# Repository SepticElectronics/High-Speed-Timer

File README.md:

# High Speed Precision Timer SEHSPT554

A simple digital timer based on the TDC7200 for high-precision, short burst time measurement with a resolution of up to 55 ps. 
Long interval, low precision time measurement is done using a 125 MHz oscillator and a DDR-type clocked synchronous counter, implemented in a MachXO2 FPGA with a theoretical resolution of 4 ns.
The data collection and interfacing is handled by an ATSAM4S Microcontroller.
Two USB 2.0 and a MicroSD Interface are available for data collection.

If connected to a PC via USB-B the device is fully USB-Bus-powered.
In the case of only using a microSD-Card or a USB thumb drive, the device must be powered from a 6-24 V Barrel Connector (5.5 x 2.1 mm or 5.5 x 2.5 mm, Center Positive).

A MIPI10 JTAG programming header is available and can be used for reprogramming the FPGA or for a boundary scan of both the FPGA and the MCU. 
A 4-Pin (2.54 mm) UART connector is provided for reprogramming the MCU.
Three SMA connectors are used with 3.3 V LVCMOS signal-level for triggering and resetting the measurements.

The PCB is designed to fit inside the Thorlabs EEB3311 housing.

*This project started out as a Product Design / Layout challenge for myself and is still in a very early WIP-stage. Any (constructive) input is very much appreciated.*
**Please note that all of the mentioned features are purely implemented on a PCB / Schematic level. No software, except for the FPGA configuration, has been written yet.**

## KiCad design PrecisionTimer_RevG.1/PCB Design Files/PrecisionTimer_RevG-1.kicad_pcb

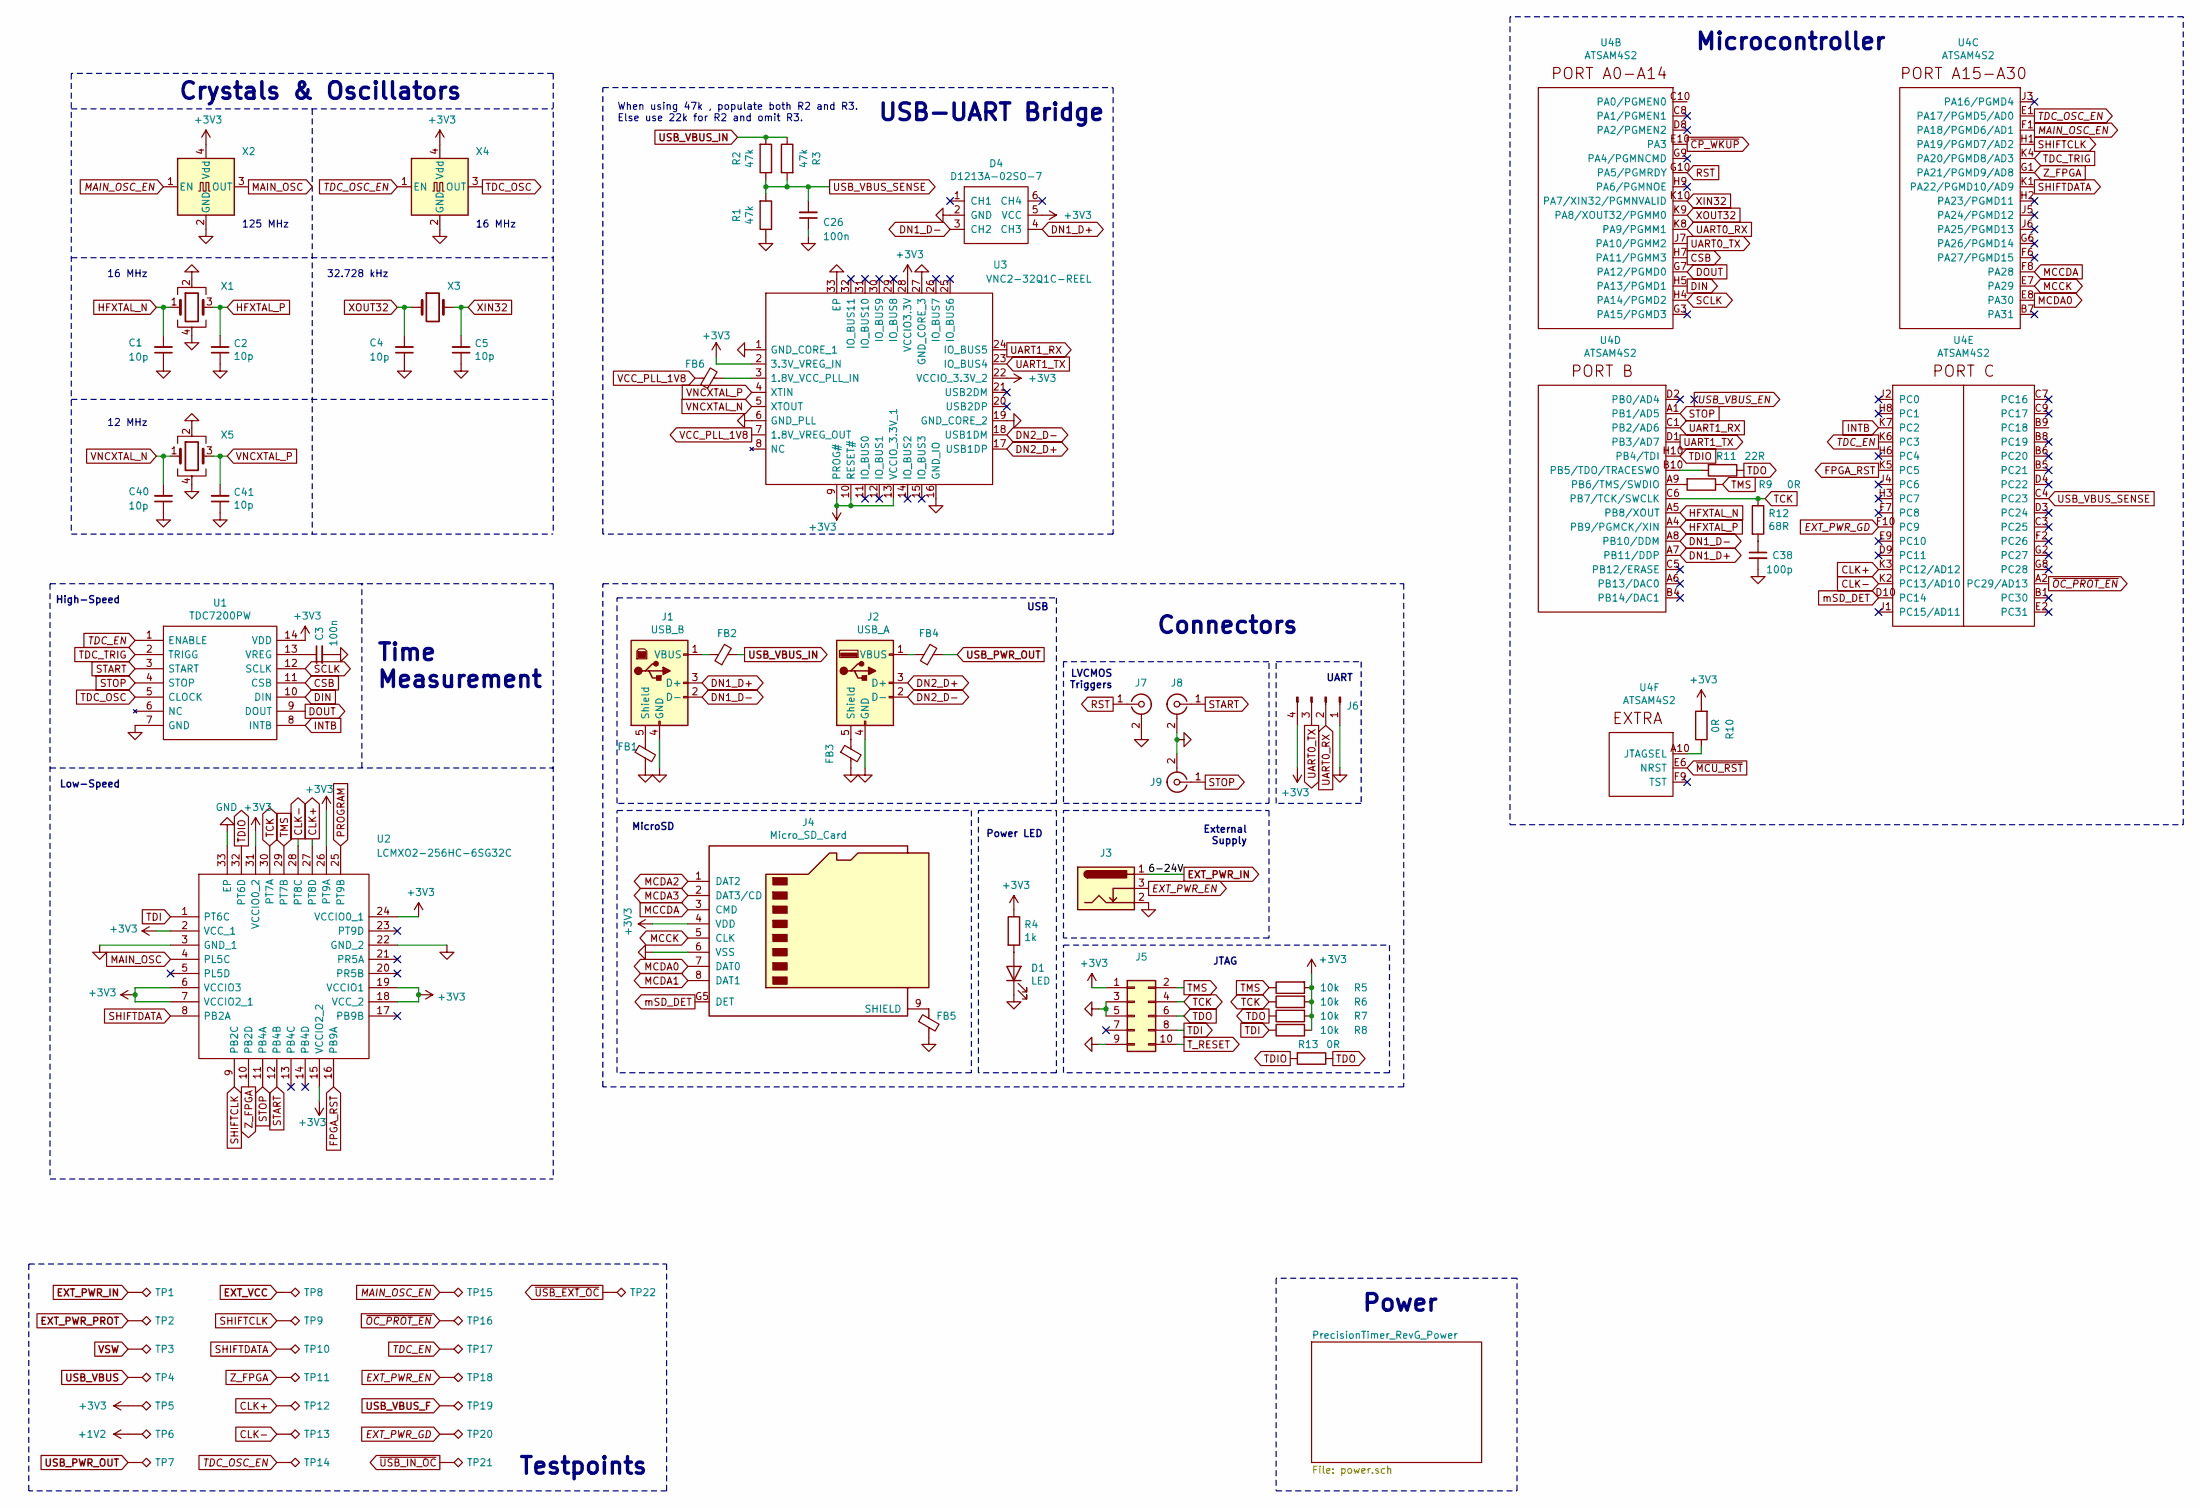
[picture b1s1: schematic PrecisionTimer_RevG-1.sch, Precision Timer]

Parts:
C1, C2, C4, C5, C40, C41: 10p; C_0402_1005Metric
C3, C26: 100n; C_0603_1608Metric
C38: 100p; C_0603_1608Metric
D1: LED; LED_D3.0mm
D4: D1213A-02SO-7; SOT-26
FB1, FB2, FB3, FB4, FB5, FB6: Ferrite 2A 330R; L_0603_1608Metric
J1: USB_B; KUSBEXSMTBS1NBTR
J2: USB_A; USB_A_Molex_67643_Horizontal
J3: Barrel_Jack_Switch; BarrelJack_Wuerth_6941xx301002
J4: Micro_SD_Card; 475710001
J5: Conn_02x05_Odd_Even; PinHeader_2x05_P1.27mm_Vertical_SMD
J6: Conn_01x04_Male; PinHeader_1x04_P2.54mm_Vertical_SMD_Pin1Left
J7, J8, J9: Conn_Coaxial; SMA_Molex_73251-2200_Horizontal
R1, R2, R3: 47k; R_0402_1005Metric
R4: 1k; R_0603_1608Metric
R5, R6, R7, R8: 10k; R_0603_1608Metric
R9, R10, R13: 0R; R_0603_1608Metric
R11: 22R; R_0603_1608Metric
R12: 68R; R_0603_1608Metric
TP1, TP3, TP5, TP6, TP12, TP13, TP14, TP15, TP21, TP22: TestPoint_Alt; TestPoint_Pad_D0.7mm
TP2, TP4, TP7, TP8, TP9, TP10, TP11, TP16, TP17, TP18, TP19, TP20: TestPoint_Alt; TestPoint_Pad_D1.0mm
U1: TDC7200PW; SOP65P640X120-14N; Manufacturer_Part_Number TDC7200PW
U2: LCMXO2-256HC-6SG32C; QFN50P500X500X60-33N; Manufacturer_Part_Number LCMXO2-256HC-4SG32I
U3: VNC2-32Q1C-REEL; QFN65P700X700X90-33N-D; Manufacturer_Part_Number VNC2-32Q1C-REEL; Mouser Part Number 895-VNC2-32Q1C-REEL
U4: ATSAM4S2; TFBGA-100_9.0x9.0mm_Layout10x10_P0.8mm
X1, X5: ECS-160-8-36B-CKY-TR; Crystal_SMD_2520-4Pin_2.5x2.0mm
X2: DSC1001DI2-125.0000; Oscillator_SMD_SeikoEpson_SG210-4Pin_2.5x2.0mm
X3: FC-135 32.7680KA-AG0; Crystal_SMD_3215-2Pin_3.2x1.5mm
X4: ECS-3225S33-160-FN-TR; Oscillator_SMD_EuroQuartz_XO32-4Pin_3.2x2.5mm

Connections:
+1V2: TP6.1; also elsewhere on the board
+3V3: D4.5 (VCC), J4.4 (VDD), J5.1, J6.4, R4.1, R5.2, R6.2, R7.2, R8.2, R10.2, TP5.1, U1.14 (VDD), U2.2 (VCC_1), U2.6 (VCCIO3), U2.7 (VCCIO2_1), U2.15 (VCCIO2_2), U2.18 (VCC_2), U2.19 (VCCIO1), U2.24 (VCCIO0_1), U2.26 (PT9A), U2.31 (VCCIO0_2), U3.2 (3.3V_VREG_IN), U3.9 (PROG#), U3.10 (RESET#), U3.13 (VCCIO_3.3V_1), U3.22 (VCCIO_3.3V_2), U3.28 (VCCIO3.3V), X2.4 (Vdd), X4.4 (Vdd); also elsewhere on the board
CLK+: TP12.1, U2.27 (PT8D), U4.K3 (PC12/AD12)
CLK-: TP13.1, U2.28 (PT8C), U4.K2 (PC13/AD10)
CSB: U1.11 (CSB), U4.H7 (PA11/PGMM3)
DIN: U1.10 (DIN), U4.H5 (PA13/PGMD1)
DN1_D+: D4.4 (CH3), J1.3 (D+), U4.A7 (PB11/DDP)
DN1_D-: D4.3 (CH2), J1.2 (D-), U4.A8 (PB10/DDM)
DN2_D+: J2.3 (D+), U3.17 (USB1DP)
DN2_D-: J2.2 (D-), U3.18 (USB1DM)
DOUT: U1.9 (DOUT), U4.G7 (PA12/PGMD0)
EXT_PWR_EN: J3.3, TP18.1; also elsewhere on the board
EXT_PWR_GD: TP20.1, U4.F10 (PC9); also elsewhere on the board
EXT_PWR_IN: J3.1, TP1.1; also elsewhere on the board
EXT_PWR_PROT: TP2.1; also elsewhere on the board
EXT_VCC: TP8.1; also elsewhere on the board
FPGA_RST: U2.16 (PB9A), U4.K5 (PC5)
GND: C1.1, C2.1, C3.2, C4.1, C5.1, C26.1, C38.2, C40.1, C41.1, D1.1 (K), D4.2 (GND), FB1.2, FB3.2, FB5.2, J1.4 (GND), J2.4 (GND), J3.2, J4.6 (VSS), J5.3, J5.5, J5.9, J6.1, J7.2 (Ext), J8.2 (Ext), J9.2 (Ext), R1.1, U1.7 (GND), U2.3 (GND_1), U2.22 (GND_2), U2.33 (EP), U3.1 (GND_CORE_1), U3.6 (GND_PLL), U3.16 (GND_IO), U3.19 (GND_CORE_2), U3.27 (GND_CORE_3), U3.33 (EP), X1.2, X1.4, X2.2 (GND), X4.2 (GND), X5.2, X5.4; also elsewhere on the board
HFXTAL_N: C1.2, U4.A5 (PB8/XOUT), X1.1
HFXTAL_P: C2.2, U4.A4 (PB9/PGMCK/XIN), X1.3
INTB: U1.8 (INTB), U4.K7 (PC2)
MAIN_OSC: U2.4 (PL5C), X2.3 (OUT)
MAIN_OSC_EN: TP15.1, U4.F1 (PA18/PGMD6/AD1), X2.1 (EN)
MCCDA: J4.3 (CMD), U4.F8 (PA28)
MCCK: J4.5 (CLK), U4.E7 (PA29)
MCDA0: J4.7 (DAT0), U4.E8 (PA30)
MCDA1: J4.8 (DAT1)
MCDA2: J4.1 (DAT2)
MCDA3: J4.2 (DAT3/CD)
unnamed: C3.1, U1.13 (VREG)
unnamed: C38.1, R12.2
unnamed: D1.2 (A), R4.2
unnamed: FB1.1, J1.5 (Shield)
unnamed: FB2.1, J1.1 (VBUS)
unnamed: FB3.1, J2.5 (Shield)
unnamed: FB4.1, J2.1 (VBUS)
unnamed: FB5.1, J4.9 (SHIELD)
unnamed: FB6.2, U3.3 (1.8V_VCC_PLL_IN)
unnamed: R9.2, U4.A9 (PB6/TMS/SWDIO)
unnamed: R10.1, U4.A10 (JTAGSEL)
unnamed: R11.2, U4.B10 (PB5/TDO/TRACESWO)
PROGRAM: U2.25 (PT9B)
RST: J7.1 (In), U4.G10 (PA5/PGMRDY)
SCLK: U1.12 (SCLK), U4.H4 (PA14/PGMD2)
SHIFTCLK: TP9.1, U2.9 (PB2C), U4.H1 (PA19/PGMD7/AD2)
SHIFTDATA: TP10.1, U2.8 (PB2A), U4.K1 (PA22/PGMD10/AD9)
START: J8.1 (In), U1.3 (START), U2.12 (PB4B)
STOP: J9.1 (In), U1.4 (STOP), U2.11 (PB4A), U4.A1 (PB1/AD5)
TCK: J5.4, R6.1, R12.1, U2.30 (PT7A), U4.C6 (PB7/TCK/SWCLK)
TDC_EN: TP17.1, U1.1 (ENABLE), U4.K6 (PC3)
TDC_OSC: U1.5 (CLOCK), X4.3 (OUT)
TDC_OSC_EN: TP14.1, U4.E1 (PA17/PGMD5/AD0), X4.1 (EN)
TDC_TRIG: U1.2 (TRIGG), U4.K4 (PA20/PGMD8/AD3)
TDI: J5.8, R8.1, U2.1 (PT6C)
TDIO: R13.2, U2.32 (PT6D), U4.H10 (PB4/TDI)
TDO: J5.6, R7.1, R11.1, R13.1
TMS: J5.2, R5.1, R9.1, U2.29 (PT7B)
T_RESET: J5.10
UART0_RX: J6.2, U4.K8 (PA9/PGMM1)
UART0_TX: J6.3, U4.J7 (PA10/PGMM2)
UART1_RX: U3.24 (IO_BUS5), U4.C1 (PB2/AD6)
UART1_TX: U3.23 (IO_BUS4), U4.D1 (PB3/AD7)
USB_PWR_OUT: FB4.2, TP7.1; also elsewhere on the board
USB_VBUS: TP4.1; also elsewhere on the board
USB_VBUS_F: TP19.1; also elsewhere on the board
USB_VBUS_IN: FB2.2, R2.2, R3.1; also elsewhere on the board
USB_VBUS_SENSE: C26.2, R1.2, R2.1, R3.2, U4.C4 (PC23)
VCC_PLL_1V8: FB6.1, U3.7 (1.8V_VREG_OUT); also elsewhere on the board
VNCXTAL_N: C40.2, U3.5 (XTOUT), X5.1
VNCXTAL_P: C41.2, U3.4 (XTIN), X5.3
VSW: TP3.1; also elsewhere on the board
XIN32: C5.2, U4.K10 (PA7/XIN32/PGMNVALID), X3.2
XOUT32: C4.2, U4.K9 (PA8/XOUT32/PGMM0), X3.1
Z_FPGA: TP11.1, U2.10 (PB2D), U4.G1 (PA21/PGMD9/AD8)
mSD_DET: J4.G5 (DET), U4.D10 (PC14)
~CP_WKUP: U4.E10 (PA3)
~MCU_RST: U4.E6 (NRST)
~OC_PROT_EN: TP16.1, U4.A2 (PC29/AD13); also elsewhere on the board
~USB_EXT_OC: TP22.1; also elsewhere on the board
~USB_IN_OC: TP21.1; also elsewhere on the board

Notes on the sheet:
Time Measurement
Connectors
Power LED
Microcontroller
LVCMOS Triggers
Low-Speed
USB
JTAG
External Supply
UART
MicroSD
USB-UART Bridge
High-Speed
Testpoints
125 MHz
16 MHz
Power
32.728 kHz
When using 47k , populate both R2 and R3. Else use 22k for R2 and omit R3.
Crystals & Oscillators
12 MHz

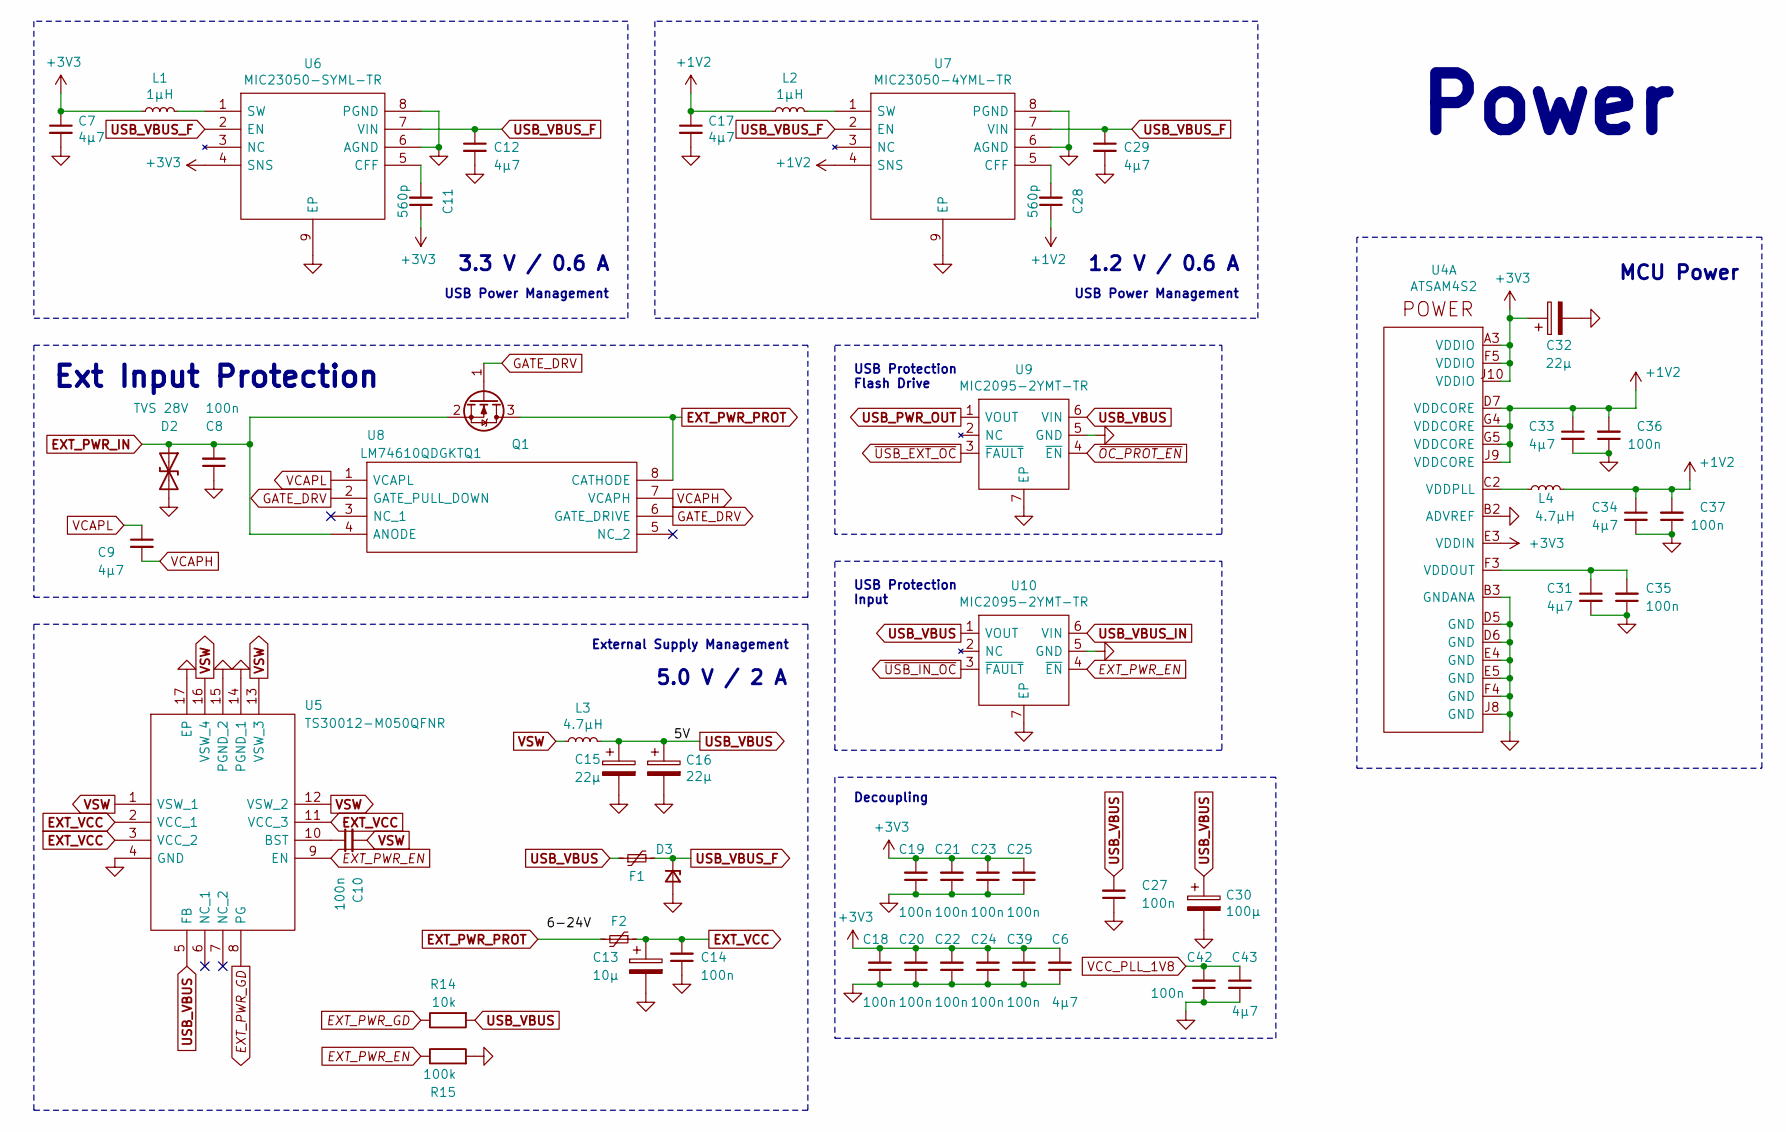
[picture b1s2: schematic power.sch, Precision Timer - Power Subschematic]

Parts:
C6, C7, C9, C12, C17, C29, C31, C33, C34, C43: 4µ7; C_0603_1608Metric
C8, C10, C14, C18, C19, C20, C21, C22, C23, C24, C25, C27, C35, C36, C37, C39, C42: 100n; C_0603_1608Metric
C11, C28: 560p; C_0603_1608Metric
C13: 10µ; C_0805_2012Metric
C15, C16, C32: 22µ; C_0805_2012Metric
C30: 100µ; C_1206_3216Metric
D2: TVS 28V; D_SMB; Voltage 30 V
D3: Zener 5.6V; D_MiniMELF
F1, F2: Polyfuse 500 mA; Fuse_1206_3216Metric_Castellated
L1, L2: 1µH; L_0805_2012Metric
L3, L4: 4.7µH; L_0805_2012Metric
Q1: NMOS 2A; SOT-23
R14: 10k; R_0603_1608Metric
R15: 100k; R_0603_1608Metric
U4: ATSAM4S2; TFBGA-100_9.0x9.0mm_Layout10x10_P0.8mm
U5: TS30012-M050QFNR; QFN50P300X300X100-17N-D; Manufacturer_Part_Number TS30012-M050QFNR; Mouser Part Number 947-TS30012-M050QFNR
U6: MIC23050-SYML-TR; SON50P200X200X90-9N; Manufacturer_Part_Number MIC23050-SYML-TR; Mouser Part Number 998-MIC23050-SYMLTR
U7: MIC23050-4YML-TR; SON50P200X200X90-9N; Manufacturer_Part_Number MIC23050-SYML-TR; Mouser Part Number 998-MIC23050-SYMLTR
U8: LM74610QDGKTQ1; SOP65P490X110-8N; Manufacturer_Part_Number LM74610QDGKTQ1; Mouser Part Number 595-LM74610QDGKTQ1
U9, U10: MIC2095-2YMT-TR; SON50P160X160X60-7N-D; Manufacturer_Part_Number MIC2095-1YMT-TR; Mouser Part Number 998-MIC2095-1YMTTR

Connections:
+1V2: C17.1, C28.1, C33.1, C34.1, C36.2, C37.2, L2.1, L4.2, U4.D7 (VDDCORE), U4.G4 (VDDCORE), U4.G5 (VDDCORE), U4.J9 (VDDCORE), U7.4 (SNS); also elsewhere on the board
+3V3: C6.2, C7.1, C11.1, C18.2, C19.2, C20.2, C21.2, C22.2, C23.2, C24.2, C25.2, C32.1, C39.2, L1.1, U4.A3 (VDDIO), U4.E3 (VDDIN), U4.F5 (VDDIO), U4.J10 (VDDIO), U6.4 (SNS); also elsewhere on the board
EXT_PWR_EN: R15.1, U5.9 (EN), U10.4 (~EN); also elsewhere on the board
EXT_PWR_GD: R14.1, U5.8 (PG); also elsewhere on the board
EXT_PWR_IN: C8.2, D2.1 (A1), Q1.2 (S), U8.4 (ANODE); also elsewhere on the board
EXT_PWR_PROT: F2.2, Q1.3 (D), U8.8 (CATHODE); also elsewhere on the board
EXT_VCC: C13.1, C14.2, F2.1, U5.2 (VCC_1), U5.3 (VCC_2), U5.11 (VCC_3); also elsewhere on the board
GATE_DRV: Q1.1 (G), U8.2 (GATE_PULL_DOWN), U8.6 (GATE_DRIVE)
GND: C6.1, C7.2, C8.1, C12.2, C13.2, C14.1, C15.2, C16.2, C17.2, C18.1, C19.1, C20.1, C21.1, C22.1, C23.1, C24.1, C25.1, C27.1, C29.2, C30.2, C31.2, C32.2, C33.2, C34.2, C35.1, C36.1, C37.1, C39.1, C42.1, C43.2, D2.2 (A2), D3.2 (A), R15.2, U4.B2 (ADVREF), U4.B3 (GNDANA), U4.D5 (GND), U4.D6 (GND), U4.E4 (GND), U4.E5 (GND), U4.F4 (GND), U4.J8 (GND), U5.4 (GND), U5.14 (PGND_1), U5.15 (PGND_2), U5.17 (EP), U6.6 (AGND), U6.8 (PGND), U6.9 (EP), U7.6 (AGND), U7.8 (PGND), U7.9 (EP), U9.5 (GND), U9.7 (EP), U10.5 (GND), U10.7 (EP); also elsewhere on the board
unnamed: C10.1, U5.10 (BST)
unnamed: C11.2, U6.5 (CFF)
unnamed: C28.2, U7.5 (CFF)
unnamed: C31.1, C35.2, U4.F3 (VDDOUT)
unnamed: L1.2, U6.1 (SW)
unnamed: L2.2, U7.1 (SW)
unnamed: L4.1, U4.C2 (VDDPLL)
USB_PWR_OUT: U9.1 (VOUT); also elsewhere on the board
USB_VBUS: C15.1, C16.1, C27.2, C30.1, F1.1, L3.2, R14.2, U5.5 (FB), U9.6 (VIN), U10.1 (VOUT); also elsewhere on the board
USB_VBUS_F: C12.1, C29.1, D3.1 (K), F1.2, U6.2 (EN), U6.7 (VIN), U7.2 (EN), U7.7 (VIN); also elsewhere on the board
USB_VBUS_IN: U10.6 (VIN); also elsewhere on the board
VCAPH: C9.2, U8.7 (VCAPH)
VCAPL: C9.1, U8.1 (VCAPL)
VCC_PLL_1V8: C42.2, C43.1; also elsewhere on the board
VSW: C10.2, L3.1, U5.1 (VSW_1), U5.12 (VSW_2), U5.13 (VSW_3), U5.16 (VSW_4); also elsewhere on the board
~OC_PROT_EN: U9.4 (~EN); also elsewhere on the board
~USB_EXT_OC: U9.3 (~FAULT); also elsewhere on the board
~USB_IN_OC: U10.3 (~FAULT); also elsewhere on the board

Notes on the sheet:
USB Power Management
Decoupling
External Supply Management
Power
USB Protection Flash Drive
3.3 V / 0.6 A
1.2 V / 0.6 A
5.0 V / 2 A
Ext Input Protection
MCU Power
USB Protection Input

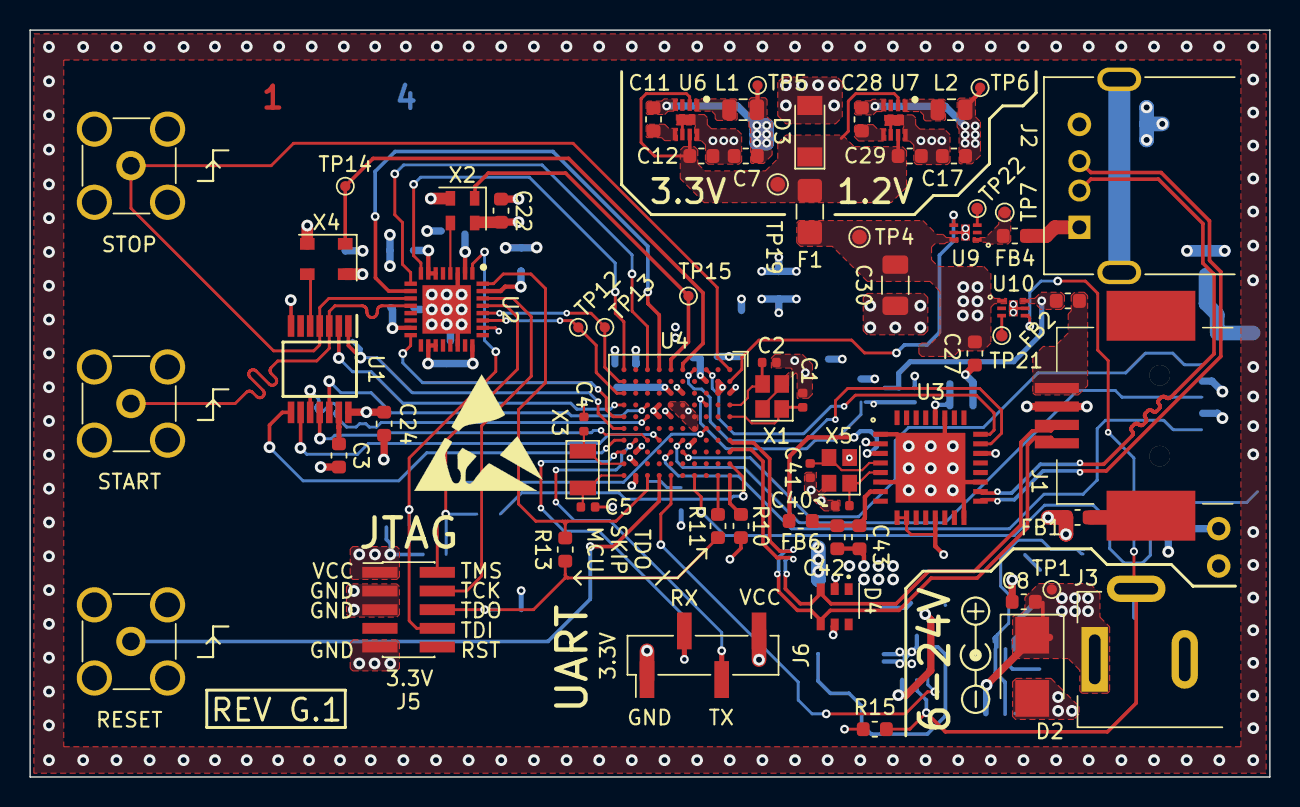
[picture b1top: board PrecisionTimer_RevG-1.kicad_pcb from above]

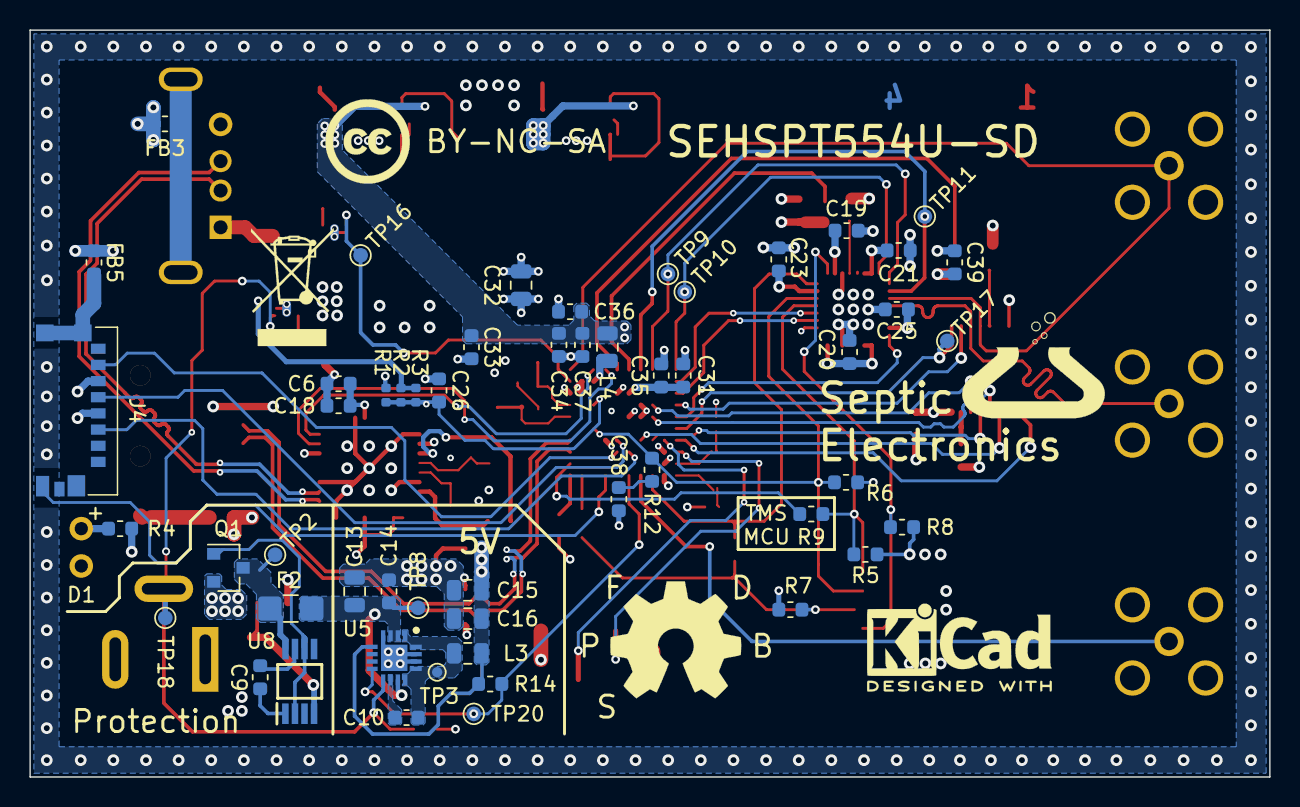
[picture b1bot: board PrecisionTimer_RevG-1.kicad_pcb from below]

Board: 4 copper layers, 84.3 x 50.8 mm, 121 parts (53 on the bottom side), 83 nets.

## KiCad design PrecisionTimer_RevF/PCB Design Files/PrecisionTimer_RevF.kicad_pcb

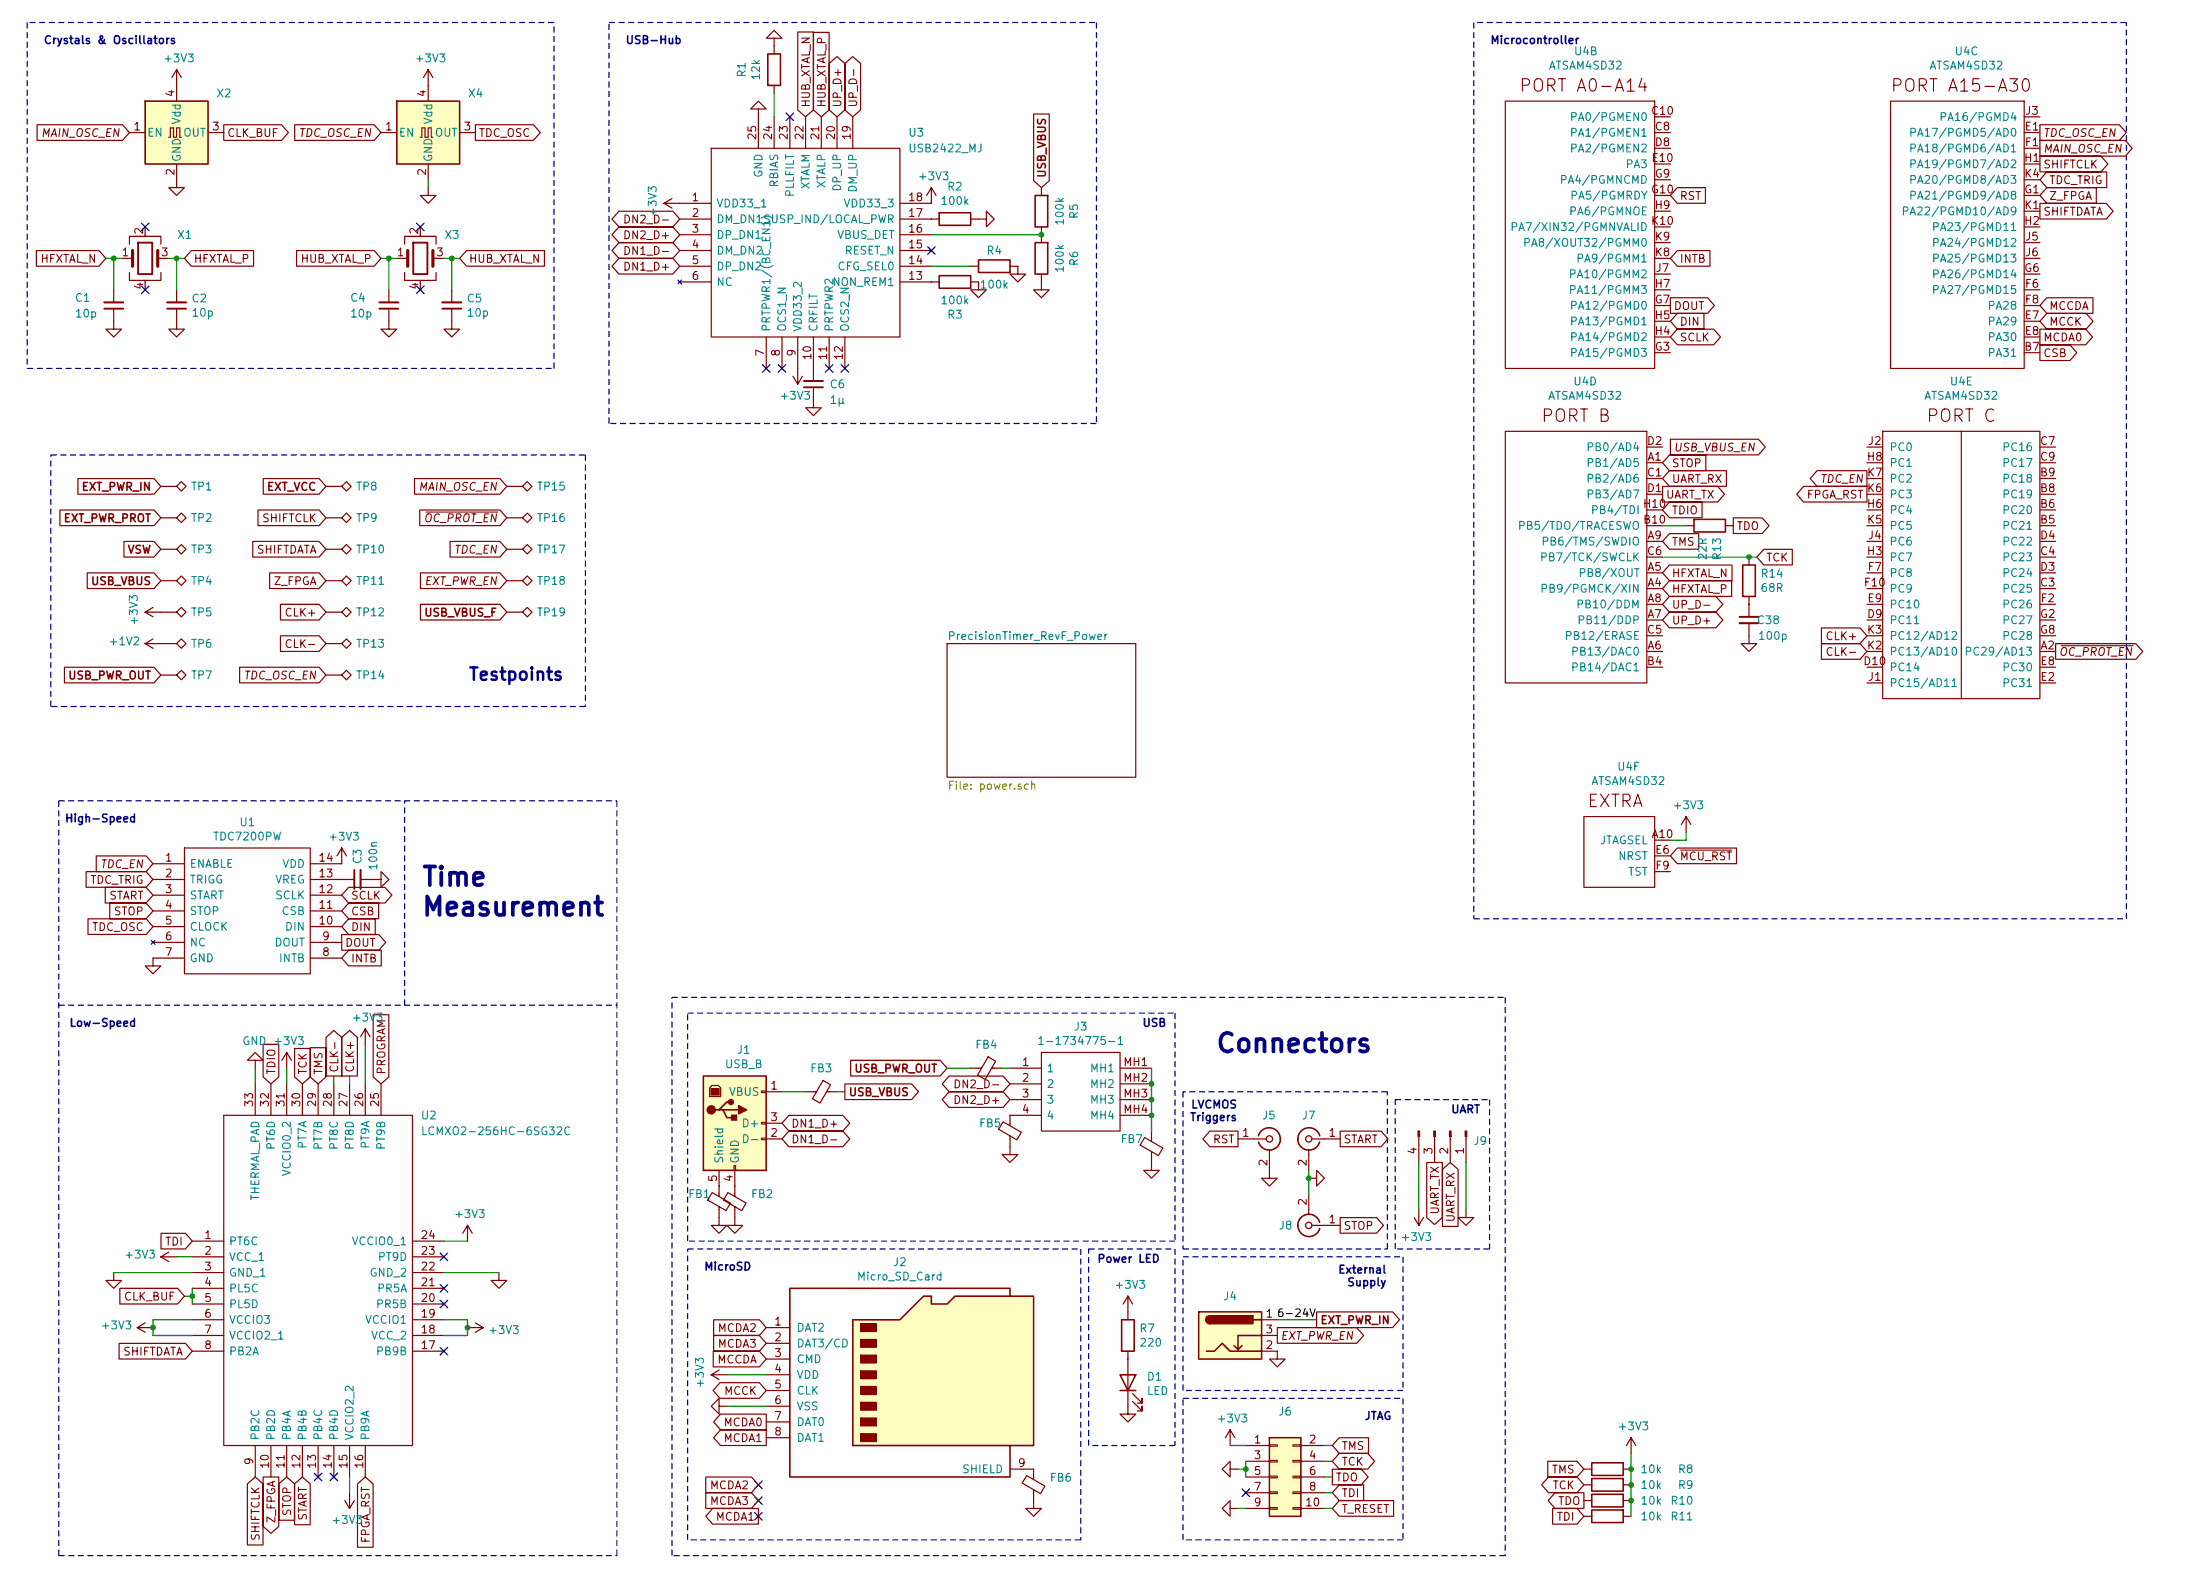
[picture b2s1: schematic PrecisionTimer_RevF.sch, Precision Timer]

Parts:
C1, C2, C4, C5: 10p; C_0402_1005Metric
C3: 100n; C_0603_1608Metric
C6: 1µ; C_0603_1608Metric
C38: 100p; C_0603_1608Metric
D1: LED; LED_D3.0mm
FB1, FB2, FB3, FB4, FB5, FB6, FB7: Ferrite_Bead_Small; L_0603_1608Metric
J1: USB_B; KUSBEXSMTBS1NBTR
J2: Micro_SD_Card; 475710001
J3: 1-1734775-1; 117347751; Mouser Part Number 571-1-1734775-1
J4: Barrel_Jack_Switch; BarrelJack_Wuerth_6941xx301002
J5, J7, J8: Conn_Coaxial; SMA_Molex_73251-2200_Horizontal
J6: Conn_02x05_Odd_Even; PinHeader_2x05_P1.27mm_Vertical_SMD
J9: Conn_01x04_Male; PinHeader_1x04_P2.54mm_Vertical_SMD_Pin1Left
R1: 12k; R_0402_1005Metric
R2, R3, R4, R5, R6: 100k; R_0402_1005Metric
R7: 220; R_0603_1608Metric
R8, R9, R10, R11: 10k; R_0603_1608Metric
R13: 22R; R_0603_1608Metric
R14: 68R; R_0603_1608Metric
TP1, TP2, TP3, TP4, TP5, TP6, TP7, TP8, TP9, TP10, TP11, TP12, TP13, TP14, TP15, TP16, TP17, TP18, TP19: TestPoint_Alt; TestPoint_Pad_D1.0mm
U1: TDC7200PW; SOP65P640X120-14N; Manufacturer_Part_Number TDC7200PW
U2: LCMXO2-256HC-6SG32C; QFN50P500X500X60-33N; Manufacturer_Part_Number LCMXO2-256HC-4SG32I
U3: USB2422_MJ; QFN50P400X400X100-25N-D; Mouser Part Number 579-USB2422/MJ
U4: ATSAM4SD32; TFBGA-100_9.0x9.0mm_Layout10x10_P0.8mm
X1: Crystal_16MHz; Crystal_SMD_2016-4Pin_2.0x1.6mm
X2: ASE-125MHz; Oscillator_SMD_SeikoEpson_SG210-4Pin_2.5x2.0mm
X3: Crystal_24MHz; Crystal_SMD_2016-4Pin_2.0x1.6mm
X4: ASE-016MHz; Oscillator_SMD_EuroQuartz_XO32-4Pin_3.2x2.5mm

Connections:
+1V2: TP6.1; also elsewhere on the board
+3V3: J2.4 (VDD), J6.1, J9.4, R7.1, R8.2, R9.2, R10.2, R11.2, TP5.1, U1.14 (VDD), U2.2 (VCC_1), U2.6 (VCCIO3), U2.7 (VCCIO2_1), U2.15 (VCCIO2_2), U2.18 (VCC_2), U2.19 (VCCIO1), U2.24 (VCCIO0_1), U2.26 (PT9A), U2.31 (VCCIO0_2), U3.1 (VDD33_1), U3.9 (VDD33_2), U3.18 (VDD33_3), U4.A10 (JTAGSEL), X2.4 (Vdd), X4.4 (Vdd); also elsewhere on the board
CLK+: TP12.1, U2.27 (PT8D), U4.K3 (PC12/AD12)
CLK-: TP13.1, U2.28 (PT8C), U4.K2 (PC13/AD10)
CLK_BUF: U2.4 (PL5C), U2.5 (PL5D), X2.3 (OUT)
CSB: U1.11 (CSB), U4.B7 (PA31)
DIN: U1.10 (DIN), U4.H5 (PA13/PGMD1)
DN1_D+: J1.3 (D+), U3.5 (DP_DN2)
DN1_D-: J1.2 (D-), U3.4 (DM_DN2)
DN2_D+: J3.3, U3.3 (DP_DN1)
DN2_D-: J3.2, U3.2 (DM_DN1)
DOUT: U1.9 (DOUT), U4.G7 (PA12/PGMD0)
EXT_PWR_EN: J4.3, TP18.1; also elsewhere on the board
EXT_PWR_IN: J4.1, TP1.1; also elsewhere on the board
EXT_PWR_PROT: TP2.1; also elsewhere on the board
EXT_VCC: TP8.1; also elsewhere on the board
FPGA_RST: U2.16 (PB9A), U4.K6 (PC3)
GND: C1.1, C2.1, C3.2, C4.1, C5.1, C6.1, C38.2, D1.1 (K), FB1.2, FB2.2, FB5.2, FB6.2, FB7.2, J2.6 (VSS), J4.2, J5.2 (Ext), J6.3, J6.5, J6.9, J7.2 (Ext), J8.2 (Ext), J9.1, R1.1, R2.1, R3.2, R4.2, R6.1, U1.7 (GND), U2.3 (GND_1), U2.22 (GND_2), U2.33 (THERMAL_PAD), U3.25 (GND), X2.2 (GND), X4.2 (GND); also elsewhere on the board
HFXTAL_N: C1.2, U4.A5 (PB8/XOUT), X1.1
HFXTAL_P: C2.2, U4.A4 (PB9/PGMCK/XIN), X1.3
HUB_XTAL_N: C5.2, U3.22 (XTALM), X3.3
HUB_XTAL_P: C4.2, U3.21 (XTALP), X3.1
INTB: U1.8 (INTB), U4.K8 (PA9/PGMM1)
MAIN_OSC_EN: TP15.1, U4.F1 (PA18/PGMD6/AD1), X2.1 (EN)
MCCDA: J2.3 (CMD), U4.F8 (PA28)
MCCK: J2.5 (CLK), U4.E7 (PA29)
MCDA0: J2.7 (DAT0), U4.E8 (PA30)
MCDA1: J2.8 (DAT1)
MCDA2: J2.1 (DAT2)
MCDA3: J2.2 (DAT3/CD)
unnamed: C3.1, U1.13 (VREG)
unnamed: C6.2, U3.10 (CRFILT)
unnamed: C38.1, R14.2
unnamed: D1.2 (A), R7.2
unnamed: FB1.1, J1.5 (Shield)
unnamed: FB2.1, J1.4 (GND)
unnamed: FB3.2, J1.1 (VBUS)
unnamed: FB4.1, J3.1
unnamed: FB5.1, J3.4
unnamed: FB6.1, J2.9 (SHIELD)
unnamed: FB7.1, J3.MH1, J3.MH2, J3.MH3, J3.MH4
unnamed: R1.2, U3.24 (RBIAS)
unnamed: R2.2, U3.17 (SUSP_IND/LOCAL_PWR)
unnamed: R3.1, U3.13 (NON_REM1)
unnamed: R4.1, U3.14 (CFG_SEL0)
unnamed: R5.1, R6.2, U3.16 (VBUS_DET)
unnamed: R13.2, U4.B10 (PB5/TDO/TRACESWO)
PROGRAM: U2.25 (PT9B)
RST: J5.1 (In), U4.G10 (PA5/PGMRDY)
SCLK: U1.12 (SCLK), U4.H4 (PA14/PGMD2)
SHIFTCLK: TP9.1, U2.9 (PB2C), U4.H1 (PA19/PGMD7/AD2)
SHIFTDATA: TP10.1, U2.8 (PB2A), U4.K1 (PA22/PGMD10/AD9)
START: J7.1 (In), U1.3 (START), U2.12 (PB4B)
STOP: J8.1 (In), U1.4 (STOP), U2.11 (PB4A), U4.A1 (PB1/AD5)
TCK: J6.4, R9.1, R14.1, U2.30 (PT7A), U4.C6 (PB7/TCK/SWCLK)
TDC_EN: TP17.1, U1.1 (ENABLE), U4.K7 (PC2)
TDC_OSC: U1.5 (CLOCK), X4.3 (OUT)
TDC_OSC_EN: TP14.1, U4.E1 (PA17/PGMD5/AD0), X4.1 (EN)
TDC_TRIG: U1.2 (TRIGG), U4.K4 (PA20/PGMD8/AD3)
TDI: J6.8, R11.1, U2.1 (PT6C)
TDIO: U2.32 (PT6D), U4.H10 (PB4/TDI)
TDO: J6.6, R10.1, R13.1
TMS: J6.2, R8.1, U2.29 (PT7B), U4.A9 (PB6/TMS/SWDIO)
T_RESET: J6.10
UART_RX: J9.2, U4.C1 (PB2/AD6)
UART_TX: J9.3, U4.D1 (PB3/AD7)
UP_D+: U3.20 (DP_UP), U4.A7 (PB11/DDP)
UP_D-: U3.19 (DM_UP), U4.A8 (PB10/DDM)
USB_PWR_OUT: FB4.2, TP7.1; also elsewhere on the board
USB_VBUS: FB3.1, R5.2, TP4.1; also elsewhere on the board
USB_VBUS_F: TP19.1; also elsewhere on the board
VSW: TP3.1; also elsewhere on the board
Z_FPGA: TP11.1, U2.10 (PB2D), U4.G1 (PA21/PGMD9/AD8)
~MCU_RST: U4.E6 (NRST)
~OC_PROT_EN: TP16.1, U4.A2 (PC29/AD13); also elsewhere on the board

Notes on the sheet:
Time Measurement
Connectors
Power LED
Microcontroller
LVCMOS Triggers
Low-Speed
USB
JTAG
External Supply
UART
Crystals & Oscillators
MicroSD
USB-Hub
High-Speed
Testpoints
